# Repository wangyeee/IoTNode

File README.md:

# IoTNode

My IoT implementation with STM32F0 and nRF24L01.

## Compile and run

1. Install [GNU Tools for ARM Embedded Processors](https://launchpad.net/gcc-arm-embedded). And execute `make` to compile the code.
2. For Linux and OS X, clone this [repo](https://github.com/texane/stlink), follow the instructions on that page and install st-util to your system.
3. Execute `make flash` to download the binray to a STM32F0 target via ST Link.

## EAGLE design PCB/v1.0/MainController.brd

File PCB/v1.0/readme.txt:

The first version of hardware, tested and working under normal circumstances. But it’s not carefully designed as I’m not a experienced hardware developer.

Reference documents:
AN4080: Getting started with STM32F0x1/x2/x8 hardware development.
RM0360: STM32F030x4/6/8/C and STM32F070x6/B advanced ARM-based 32-bit MCUs Reference manual.
STM32F072B Discovery board schematics.

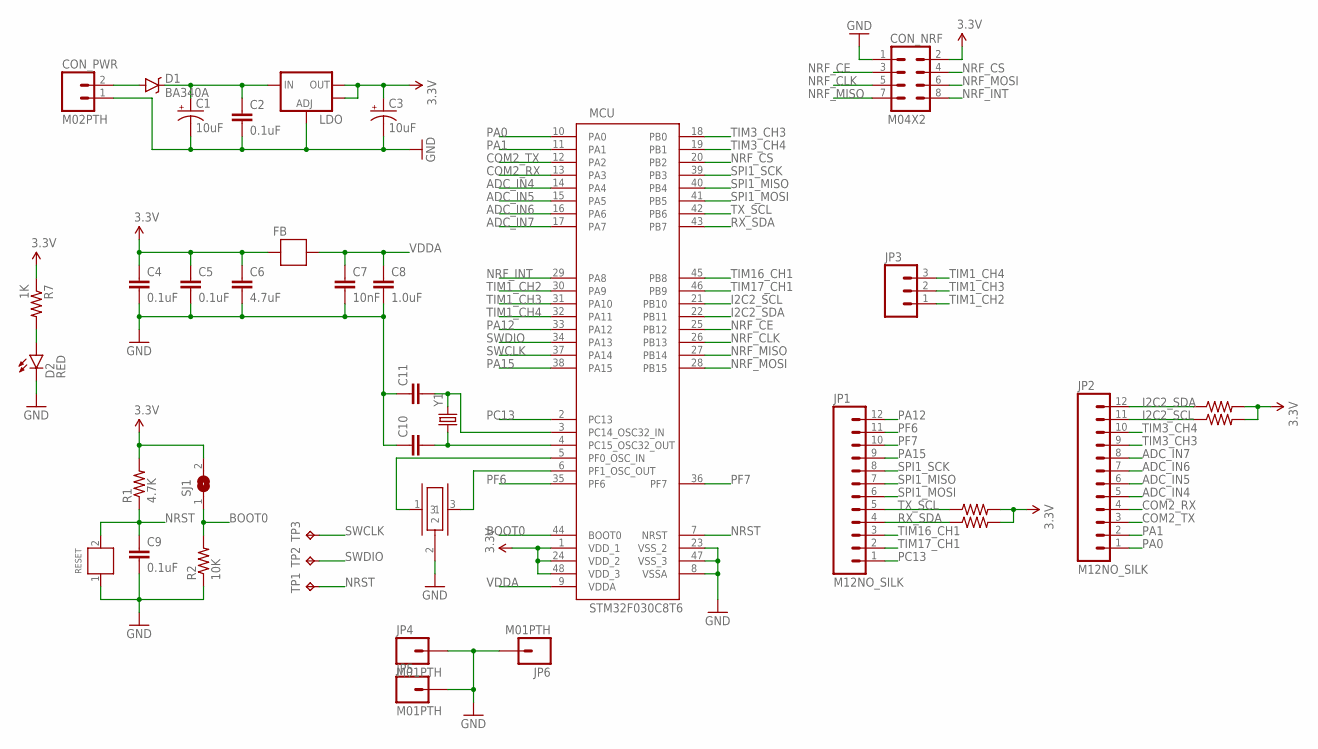
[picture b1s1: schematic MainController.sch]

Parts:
C1, C3: 10uF; EIA3216
C2, C4, C5, C9: 0.1uF; 0603-CAP
C6: 4.7uF; 0603-CAP
C7: 10nF; 0603-CAP
C8: 1.0uF; 0603-CAP
C10, C11: CAP0603-CAP; 0603-CAP
CON_NRF: M04X2; 2X4
CON_PWR: M02PTH; 1X02
D1: BA340A; SMA-DIODE
D2: RED; LED-0603
FB: FBFB0805; 0805W
JP1, JP2: M12NO_SILK; 1X12_NO_SILK
JP3: M031X03_NO_SILK; 1X03_NO_SILK
JP4, JP5, JP6: M01PTH; 1X01
LDO: V_REG_LM1117SOT223; SOT223
MCU: STM32F030C8T6; TQFP48
OSC: CSTCE8M00G52-R0; CSTCE_M_G
R1: 4.7K; 0603-RES
R2, R3, R4, R5, R6: 10K; 0603-RES
R7: 1K; 0603-RES
RESET: SWITCH_SMD; SWITCH3X6_SMD
SJ1: SJ
TP1, TP2, TP3: TPB1,27; B1,27
Y1: CRYSTALTC38H; TC38H

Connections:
3.3V: C3.A (+), C4.1, C5.1, C6.1, CON_NRF.2, FB.2, LDO.2 (OUT), LDO.4 (OUT), MCU.1 (VDD_1), MCU.24 (VDD_2), MCU.48 (VDD_3), R1.2, R3.2, R4.2, R5.2, R6.2, R7.1, SJ1.2
ADC_IN4: JP2.5, MCU.14 (PA4)
ADC_IN5: JP2.6, MCU.15 (PA5)
ADC_IN6: JP2.7, MCU.16 (PA6)
ADC_IN7: JP2.8, MCU.17 (PA7)
BOOT0: MCU.44 (BOOT0), R2.2, SJ1.1
COM2_RX: JP2.4, MCU.13 (PA3)
COM2_TX: JP2.3, MCU.12 (PA2)
GND: C1.C (-), C2.2, C3.C (-), C4.2, C5.2, C6.2, C7.2, C8.2, C9.2, C10.1, C11.1, CON_NRF.1, CON_PWR.1, D2.C, JP4.1, JP5.1, JP6.1, LDO.1 (ADJ), MCU.8 (VSSA), MCU.23 (VSS_2), MCU.47 (VSS_3), OSC.2, R2.1, RESET.1
I2C2_SCL: JP2.11, MCU.21 (PB10), R5.1
I2C2_SDA: JP2.12, MCU.22 (PB11), R6.1
unnamed: MCU.5 (PF0_OSC_IN), OSC.1
unnamed: MCU.6 (PF1_OSC_OUT), OSC.3
unnamed: C1.A (+), C2.1, D1.C, LDO.3 (IN)
unnamed: C10.2, MCU.4 (PC15_OSC32_OUT), Y1.1
unnamed: C11.2, MCU.3 (PC14_OSC32_IN), Y1.2
unnamed: CON_PWR.2, D1.A
unnamed: D2.A, R7.2
NRF_CE: CON_NRF.3, MCU.25 (PB12)
NRF_CLK: CON_NRF.5, MCU.26 (PB13)
NRF_CS: CON_NRF.4, MCU.20 (PB2)
NRF_INT: CON_NRF.8, MCU.29 (PA8)
NRF_MISO: CON_NRF.7, MCU.27 (PB14)
NRF_MOSI: CON_NRF.6, MCU.28 (PB15)
NRST: C9.1, MCU.7 (NRST), R1.1, RESET.2, TP1.TP
PA0: JP2.1, MCU.10 (PA0)
PA1: JP2.2, MCU.11 (PA1)
PA12: JP1.12, MCU.33 (PA12)
PA15: JP1.9, MCU.38 (PA15)
PC13: JP1.1, MCU.2 (PC13)
PF6: JP1.11, MCU.35 (PF6)
PF7: JP1.10, MCU.36 (PF7)
RX_SDA: JP1.4, MCU.43 (PB7), R4.1
SPI1_MISO: JP1.7, MCU.40 (PB4)
SPI1_MOSI: JP1.6, MCU.41 (PB5)
SPI1_SCK: JP1.8, MCU.39 (PB3)
SWCLK: MCU.37 (PA14), TP3.TP
SWDIO: MCU.34 (PA13), TP2.TP
TIM1_CH2: JP3.1, MCU.30 (PA9)
TIM1_CH3: JP3.2, MCU.31 (PA10)
TIM1_CH4: JP3.3, MCU.32 (PA11)
TIM3_CH3: JP2.9, MCU.18 (PB0)
TIM3_CH4: JP2.10, MCU.19 (PB1)
TIM16_CH1: JP1.3, MCU.45 (PB8)
TIM17_CH1: JP1.2, MCU.46 (PB9)
TX_SCL: JP1.5, MCU.42 (PB6), R3.1
VDDA: C7.1, C8.1, FB.1, MCU.9 (VDDA)

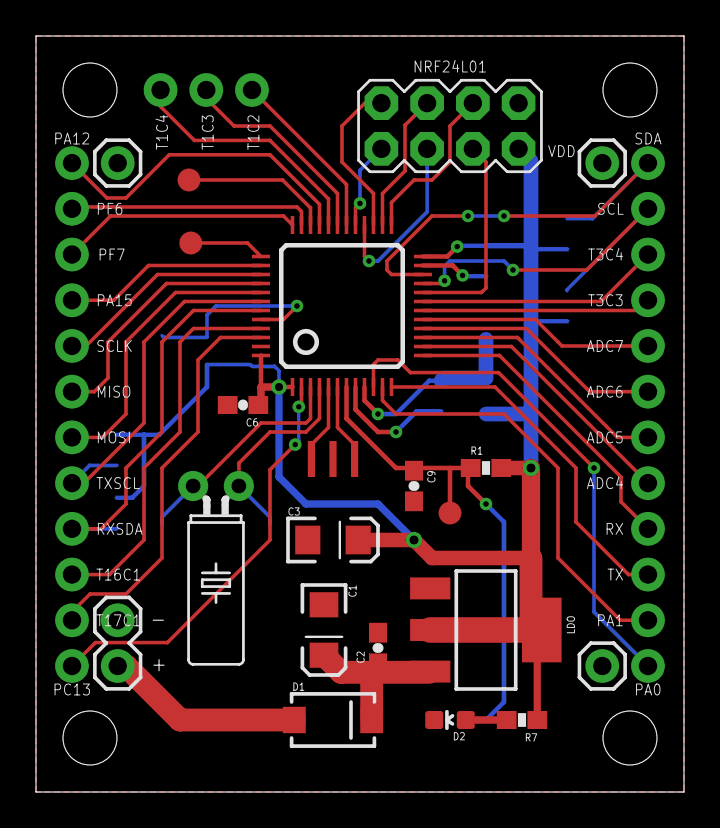
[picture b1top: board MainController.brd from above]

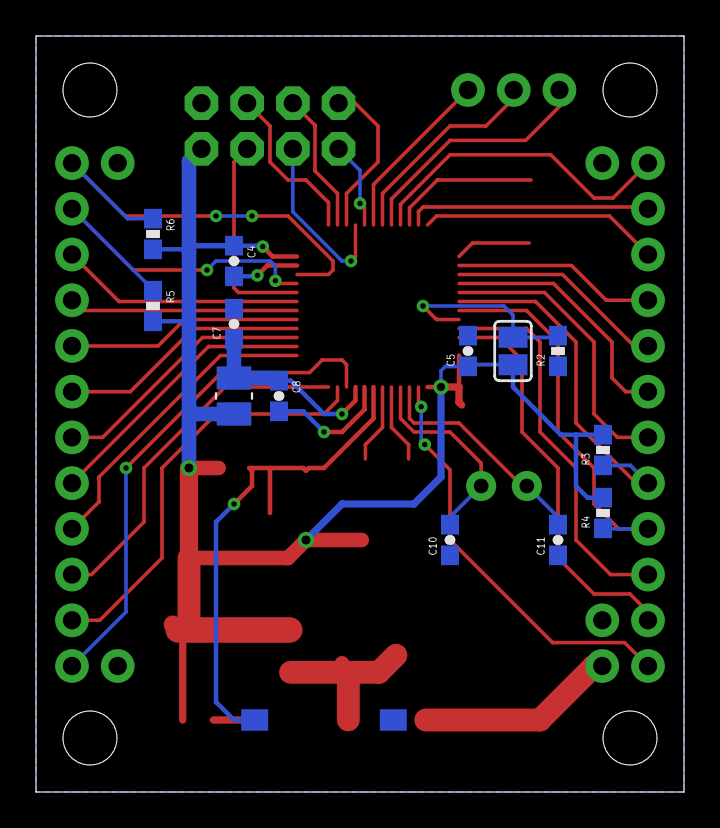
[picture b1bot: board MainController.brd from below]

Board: 2 copper layers, 36.0 x 42.0 mm, 38 parts (14 on the bottom side), 47 nets.

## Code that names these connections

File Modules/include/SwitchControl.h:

#ifndef _SWITCHCONTROL_H_
#define _SWITCHCONTROL_H_

#ifdef __cplusplus
extern "C" {
#endif

#ifdef STM32F0XX
#include "stm32f0xx.h"
#include "gpio.h"
#endif

#include "NodeLink.h"

#define NUMBER_OF_SWITCHES 7

/*
 * id  GPIO
 *  0  PA0
 *  1  PA1
 *  2  PA12
 *  3  PA15
 *  4  PC13
 *  5  PF6
 *  6  PF7
 */
typedef struct _switch_t {
    uint8_t id : 4;
    uint8_t status : 2;
    uint8_t enabled : 2;
    uint8_t (*pack)(struct _switch_t* sw, uint8_t* buf, uint8_t len);
    uint8_t (*unpack)(struct _switch_t* sw, uint8_t* buf, uint8_t len);
#ifndef STM32F0XX
/* Compile for server */
    node_t node;
#endif
} __attribute__ ((__packed__)) switch_t;

#define SWITCH_SIZE sizeof(switch_t)

typedef enum {
    OFF = 0,
    ON
} switch_status;

#ifdef STM32F0XX

void init_switches(void);
uint8_t switch_message_listener(node_t from, uint8_t* msg, uint8_t len);

#endif /* STM32F0XX */

/**
 * 0 1 2 3 | 4 5     | 6 7
 * id      | enabled | status
 */
static uint8_t switch_pack(struct _switch_t* sw, uint8_t* buf, uint8_t len) {
    if (len > 0) {
        buf[0] = (uint8_t) ((sw->id << 4) | (sw->enabled << 2) | sw->status);
        return 1;
    }
    return 0;
}

static uint8_t switch_unpack(struct _switch_t* sw, uint8_t* buf, uint8_t len) {
    if (len > 0) {
        sw->id = (buf[0] & 0b11110000) >> 4;
        sw->enabled = ((buf[0] & 0b00001100) >> 2) ? ENABLED : DISABLED;
        sw->status = (buf[0] & 0b00000011) ? ON : OFF;
        return 1;
    }
    return 0;
}

static void init_switch_type(switch_t* sw) {
    sw->enabled = DISABLED;
    sw->id = 0;
    sw->status = OFF;
    sw->pack = switch_pack;
    sw->unpack = switch_unpack;
}

#ifdef __cplusplus
}
#endif
#endif /* _SWITCHCONTROL_H_ */

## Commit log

2015-03-30 Initial commit.
2015-03-31 Add analog and digital IO support.
2015-04-01 Add PWM output support.
2015-04-12 Add ILI9163C LCD driver support.
2015-04-18 Tested nRF24L01 driver.
2015-04-19 Add NodeLink for communication between nodes.
2015-04-25 Add build configuration file. Tested SPI2Serial bridge. Added switch test code.
2015-04-25 Add readme file.
2015-04-27 Add switch control module.
2015-04-28 Fixed careless macro definition error.
2015-05-07 Refactoring switch control code with NodeLink. 1. Adding pack/unpack function for control struct to deal with bit order issue. 2. Adding test cases to test switch control without a PHP application se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
2015-05-10 Modify serial SPI bridge for consistence issue.
2015-05-10 Add 1.0 version of PCB desgin.

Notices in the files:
parts and their libraries:
SparkFun-Capacitors: Licensing: Creative Commons ShareAlike 4.0 International - https://creativecommons.org/licenses/by-sa/4.0
